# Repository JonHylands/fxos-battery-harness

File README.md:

fxos-battery-harness
====================

Repository for Battery Harness &amp; Ammeter source/design files (CAD, PCB, etc)

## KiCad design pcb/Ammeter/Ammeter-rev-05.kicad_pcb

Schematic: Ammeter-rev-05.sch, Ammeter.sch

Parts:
C1, C2: 18pF; c_0603
C3, C12: 1uF; c_0603
C4, C5, C6, C7, C10, C14, C16: 0.1uF; c_0603
C8: 22uF; c_1206
C9, C15: 4.7uF; c_0603
C11: 10uF; c_0603
C13: 20nF; c_0603
CON1, CON2: USB-MICRO-B; USB_MINI_B_AMMETER
D1, D2, D3: LED; LED-0603
J1: Program; SIL_6_050
J2: BATTERY; SIL_3_050
J3: CONSOLE; SIL_3_050
J4: USB
P1: CONN_2
R1, R5, R7: 220; SM0603
R2, R3: 22; SM0603
R4, R9, R10, R11, R12: 10K; SM0603
R6: 1M; SM0603
R8: 0; SM0603
SENSE1: 0.1; SM1206
SW1: SW_PUSH; PUSH_SMT
U1: ATMEGA32U4; atmel-TQFP44
U2, U6: SIP32411; sc70-6
U3: ZXCT1041; sot323-5
U4: AD7680; sot323-6
U5: ADP160-4.2; sot323-5
U7: AO3415
U8: FSUSB42
X1: 16MHz; CRYSTAL_SMT

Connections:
BATT_DIR: R6.2, U1.28, U3.1 (FLAG)
CS: U1.22, U4.4 (/CS)
GND: C1.1, C2.1, C3.2, C4.1, C5.1, C6.1, C7.1, C8.1, C9.1, C10.1, C11.1, C12.1, C13.1, C14.1, C15.1, C16.1, CON1.5 (GND), CON1.6 (SHELL1), CON1.7 (SHELL2), CON1.8 (SHELL3), CON1.9 (SHELL4), CON2.5 (GND), CON2.6 (SHELL1), CON2.7 (SHELL2), CON2.8 (SHELL3), CON2.9 (SHELL4), D1.2 (K), D2.2 (K), D3.2 (K), J1.6, J2.3, J3.1, J4.4 (GND), J4.5 (Shield_1), J4.6 (Shield_2), P1.2 (PM), R9.2, R10.2, SW1.2, U1.5, U1.15, U1.23, U1.35, U1.43, U2.2 (GND), U2.5 (GND2), U3.2 (GND), U4.2 (GND), U5.2 (GND), U6.2 (GND), U6.5 (GND2), U8.2 (Sel), U8.5 (GND)
LED: R5.2, U1.1
unnamed: C14.2, U1.41, U6.1 (OUT)
unnamed: R9.1, U1.37, U6.3 (EN)
unnamed: J3.2 (PM), U1.21
unnamed: J3.3, U1.20
unnamed: J2.2 (PM), SENSE1.2, U3.5 (S-)
unnamed: R8.1, U3.3 (OUT)
unnamed: C13.2, R8.2, U4.3 (Vin)
unnamed: R7.2, R10.1, U1.30, U2.3 (EN)
unnamed: J4.1 (Vbus), U7.3 (Drain)
unnamed: R11.2, U1.8, U7.1 (Gate)
unnamed: CON2.1 (VBUS), U7.2 (Source)
unnamed: J4.2 (D-), U8.6 (HSD1-)
unnamed: J4.3 (D+), U8.7 (HSD1+)
unnamed: U1.12, U8.10 (/OE)
unnamed: P1.1, R12.1, U1.40
unnamed: C11.2, U4.1 (Vcc), U5.5 (VOUT)
unnamed: CON2.2 (D-), U8.4 (D-)
unnamed: CON2.3 (D+), U8.3 (D+)
unnamed: C9.2, C15.2, J2.1, U2.4 (N/C), U6.4 (N/C)
unnamed: J1.1, U1.11
unnamed: J1.4, U1.10
unnamed: J1.3, U1.9
unnamed: C3.1, U1.6
unnamed: CON1.2 (D-), R2.1
unnamed: D2.1 (A), R1.1
unnamed: R2.2, U1.3
unnamed: CON1.3 (D+), R3.1
unnamed: D1.1 (A), R5.1
unnamed: C1.2, U1.17, X1.1
unnamed: R3.2, U1.4
unnamed: D3.1 (A), R7.1
unnamed: C2.2, U1.16, X1.2
unnamed: C10.2, SENSE1.1, U2.1 (OUT), U3.4 (S+)
RESET: J1.5, R4.2, SW1.1
SCLK: U1.18, U4.6 (SCLK)
SDATA: U1.19, U4.5 (SDATA)
VCC: C4.2, C5.2, C6.2, C7.2, C8.2, C12.2, C16.2, CON1.1 (VBUS), J1.2, R1.2, R4.1, R6.1, R11.1, R12.2, U1.2, U1.7, U1.14, U1.24, U1.34, U1.44, U5.1 (VIN), U5.3 (EN), U8.1 (VCC)

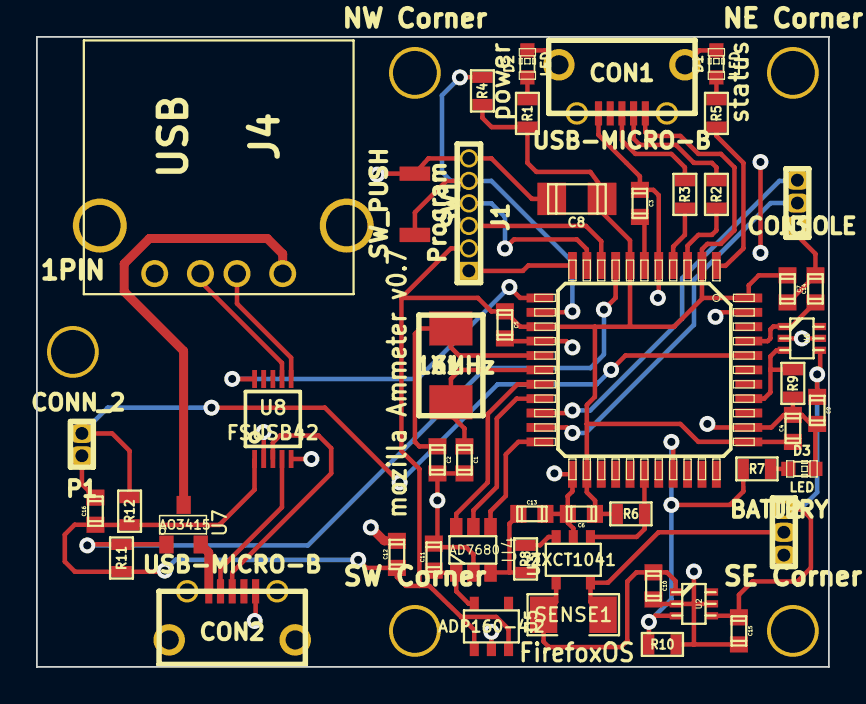
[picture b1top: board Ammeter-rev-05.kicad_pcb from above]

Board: 2 copper layers, 44.0 x 35.0 mm, 54 parts (0 on the bottom side), 41 nets.

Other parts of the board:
1PIN: CornerPin
NE Corner: CornerPin
NW Corner: CornerPin
SE Corner: CornerPin
SW Corner: CornerPin

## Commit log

2013-12-13 Initial revisions of pcb/cad files
2015-03-27 Added rev 5 (extended ammeter with USB switch) (uses KiCAD)
2015-03-27 Added rev 5 gerber files
2015-03-27 Added extended ammeter housing 3D model
